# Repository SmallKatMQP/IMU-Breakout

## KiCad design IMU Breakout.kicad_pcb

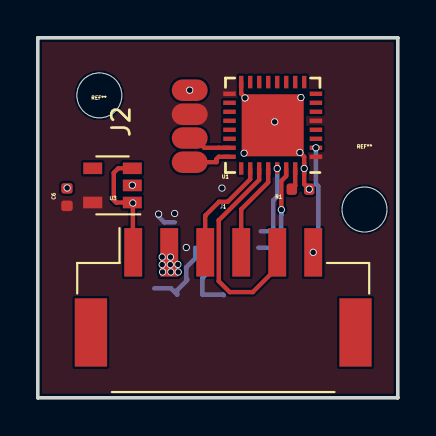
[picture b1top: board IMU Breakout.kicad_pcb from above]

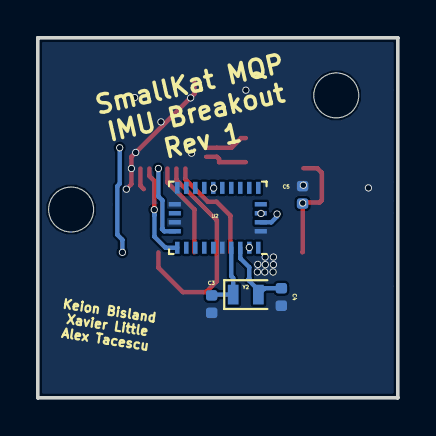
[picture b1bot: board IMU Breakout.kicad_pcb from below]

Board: 2 copper layers, 20.0 x 20.0 mm, 11 parts (5 on the bottom side), 14 nets.

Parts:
C3, C4: 10PF; C_0402_1005Metric
C5, C6: 1UF; C_0402_1005Metric
J1: Conn_01x06_Male; Molex_CLIK-Mate_502494-0670_1x06-1MP_P2.00mm_Horizontal
J2: Conn_01x04_Female; 1x4Pads
R1: R; R_0402_1005Metric
U1: STM32L432KCUx; QFN-32-1EP_5x5mm_P0.5mm_EP3.45x3.45mm
U2: BNO055; LGA-28_5.2x3.8mm_P0.5mm
U3: MIC5501-3.0YM5; SOT-23-5
Y2: Crystal; Crystal_SMD_2012-2Pin_2.0x1.2mm

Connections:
+3V3: C6.2, J2.3, U1.1, U1.5, U1.17, U2.3, U2.4, U2.11, U2.28, U3.5
+BATT: C5.2, J1.1, U3.1, U3.3
CS: J1.6, U1.2
GND: C3.1, C4.1, C5.1, C6.1, J1.2, J2.4, R1.1, U1.16, U1.32, U1.33, U2.2, U2.15, U2.16, U2.18, U2.25, U3.2
MISO: J1.5, U1.27
MOSI: J1.4, U1.28
unnamed: C3.2, U2.26, Y2.1
unnamed: C4.2, U2.27, Y2.2
unnamed: R1.2, U1.31
SCK: J1.3, U1.26
SCL: U1.29, U2.19
SDA: U1.30, U2.20
SWCLK: J2.1, U1.24
SWDIO: J2.2, U1.23

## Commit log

2018-08-27 Added all files for V1
2018-10-24 added uart and programming
